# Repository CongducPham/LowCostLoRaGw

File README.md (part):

Low-cost LoRa IoT framework developed in the EU H2020 WAZIUP/WAZIHUB projects
=====================================================================

We are not maintaining this repo anymore
----------------------------------------

First of all, thank you for all the stars you gave us! We started the work on low-cost LoRa gateway back in 2015. It has been a great challenge for us and we learned a lot. We also hope that this early work has been useful for you in your projects. As we collaborated with WAZIUP e.V. on the development of a more efficient gateway software, some of our code served as foundation for a new development line called WaziGate by WAZIUP e.V. team who is doing a great work! In 2021, we completely shifted to this WaziGate distribution to build the edge-enabled LoRa gateway for the [PRIMA INTEL-IRRIS project](https://intel-irris.eu). You can read more detail on the dedicated [INTEL-IRRIS GitHub repo](https://github.com/CongducPham/PRIMA-Intel-IrriS). Then, in 2025, as our works in INTEL-IRRIS are continuing in the [PEPR AgriFutur project](https://iotsensingsystem.live-website.com/pepr-agroeconum-agrifutur), at time of writing, the latest edge-enabled gateway we are building on top of the general WaziGate framework provided by WAZIUP e.V is available from the dedicated [PEPR AgriFutur GitHub](https://github.com/CongducPham/PEPR_AgriFutur). Check our latest development on this GitHub repo. 

News from EU commission
-----------------------

- April 12th, 2022. European Internet of Things technology supports innovation in Africa: [two EU-Africa innovation projects have succeeded in rolling out advanced digital technologies to support entrepreneurship in sub-Saharan Africa](https://digital-strategy.ec.europa.eu/en/news/european-internet-things-technology-supports-innovation-africa).

- June 19th, 2020. The low-cost, low-power and long-distance cattle collar developed in the EU H2020 WAZIUP project has been identified by the European Commission's Innovation Radar! See more information at the end of this page.

Latest news
-----------

- **NEW-Dec22** Both the 32-bit OS and the 64-bit OS have now been upgraded and tested for RPI4 (including CM4). See [README](https://github.com/CongducPham/LowCostLoRaGw/blob/master/gw_full_latest/README-WiringPi-64bit-OS.md) for RPI4 and/or 64-bit OS.

- **NEW-Oct21** We have now a beta version of the whole low-cost Raspberry-based gateway with embedded advanced AI frameworks. The embedded AI framework will be used in PRIMA [INTEL-IRRIS project](http://intel-irris.eu/) to build low-cost and smart irrigation systems for smallholders. Follow INTEL-IRRIS [Twitter channel](https://twitter.com/Intel_IrriS) for updates. See [README](https://github.com/CongducPham/LowCostLoRaGw/blob/master/gw_full_latest/README-AI.md) on AI framework. Download the 64-bit RaspiOS SD image to be flashed on a 32GB class 10 SD card, see below for download links.

- **NEW-Jan21** To provide support for next 64-bit OS, the low-level SPI library on the Raspberry gateway has moved from Libelium's `arduPi` lib to Gordon's `wiringPi` lib because `arduPi` relies heavily on direct memory accesses that are difficult to port. The main reason for 64-bit OS is to prepare the whole low-cost Raspberry-based gateway to embed advanced AI frameworks that are mostly based on 64-bit OS. See [README](https://github.com/CongducPham/LowCostLoRaGw/blob/master/gw_full_latest/README-WiringPi-64bit-OS.md) for RPI4 and/or 64-bit OS. **`wiringPi` is now the default low-level SPI layer in the GitHub source distribution.**

- **NEW-Nov20** To support the new SX126X and SX128X LoRa chips, we updated and added Arduino ProMini PCBs to easily connect NiceRF SX1262 and NiceRF SX1280 modules. These modules have same size than the HopeRF RFM95W for SX1276.

- **NEW-Oct20** The low-level radio communication library has moved to the SX12XX LoRa library from Stuart Robinson in order to build devices and gateways with **SX126X, SX127X and SX128X LoRa chip**. The default gateway program is compiled for an SX127X based module using the SX12XX library. This is a major move to provide support for the most recent LoRa chips including those for 2.4GHz LoRa. See [README](https://github.com/CongducPham/LowCostLoRaGw/blob/master/gw_full_latest/README-SX12XX.md) on porting to SX12XX library.

Quick start
-----------
- **Beta version of RaspiOS (Debian Buster 64-bit) with AI framework is ready for testing!** It has everything you need (all features of 32-bit version) + the embedded AI framework. [zipped 8GB SD card image from GoogleDrive](https://drive.google.com/uc?export=download&id=1UzSULM2TjCKWjVWIvHqLy6Iu_FR_1Xmo). The image is about 3GB for download. You can take the 8GB image for flashing on 16GB or 32GB SD card and use `raspi-config` to expand the file system. 
- **The current SD card image (Debian Buster 32-bit) has everything you need!** [zipped 8GB SD card image from GoogleDrive](https://drive.google.com/uc?export=download&id=1ZiIpA_PfARHPmQetJ25iZnfyjeD8Rm3j). To be flashed on a 8GB class 10 SD card. See [installation section](https://github.com/CongducPham/LowCostLoRaGw#installing-the-latest-gateway-version). 
- Use the single-channel gateway for LoRaWAN-like communication (including downlink) with LoRa 2.4GHz. Upload to TTN or ChirpStack network servers. See [README](https://github.com/CongducPham/LowCostLoRaGw/blob/master/gw_full_latest/README-SX12XX.md)
- Use the single-channel gateway for limited LoRaWAN (including downlink and OTAA feature) on the 433MHz band for devices with our [modified LMIC](https://github.com/CongducPham/LMIC_low_power#using-433mhz-band)
- The single-channel gateway now also provides LoRaWAN downlink and OTAA features for devices with our [modified LMIC](https://github.com/CongducPham/LMIC_low_power#using-single-channel-gateway). See updated [README](https://github.com/CongducPham/LowCostLoRaGw/blob/master/gw_full_latest/README-downlink.md)
- Includes support of the open-source ChirpStack LoRaWAN Network Server, see [README](https://github.com/CongducPham/LowCostLoRaGw/blob/master/gw_full_latest/scripts/chirpstack/README.md)
- Support of multi-channel RPI SX1301 LoRaWAN gateway: benefit from the open, versatile, multi-cloud Low-cost LoRa IoT framework with the flexibility and scalability of a multi-channel LoRaWAN gateway, see [README](https://github.com/CongducPham/LowCostLoRaGw/blob/master/gw_full_latest/scripts/rak2245-rak831/README.md)
- We have a new online [Arduino-Sensor-LoRa tutorial](http://cpham.perso.univ-pau.fr/LORA/WAZIUP/tuto/index.html) and here is the direct link to the [LoRa part](http://cpham.perso.univ-pau.fr/LORA/WAZIUP/tuto/sensors/lora_sensor/Arduino_lora_demo.html)
- Read the [Low-cost-LoRa-device leaflet](https://github.com/CongducPham/tutorials/blob/master/Low-cost-LoRa-device-leaflet.pdf)
- Read the [Low-cost-LoRa-GW leaflet](https://github.com/CongducPham/tutorials/blob/master/Low-cost-LoRa-GW-leaflet.pdf)
- Look at the [Low-cost-LoRa-GW web admin interface tutorial](https://github.com/CongducPham/tutorials/blob/master/Low-cost-LoRa-GW-web-admin.pdf). For most end-users, the web admin interface is sufficient to configure and manage the gateway. **For instance, to configure a new gateway, it is recommended to use the web admin interface to update the gateway software and to run the basic configuration procedure as described [here](https://github.com/CongducPham/LowCostLoRaGw#option-i)**
- **The rest of this README file contains additional information to better understand the proposed low-cost IoT framework**.

PCBs
----

In order to facilitate connection between an Arduino board or a RaspberryPI and the well-known RFM95W (SX1276) LoRa radio module, we developed simple PCBs for Arduino ProMini, Arduino Nano and RaspberryPI and make them **freely** available. 

The first PCB is a simple RFM95W breakout with header pins for both the Raspberry (mainly to make a gateway) and Arduino boards. The RFM95W breakout initially designed for the HopeRF RFM95W (referred to as old RFM95W breakout) can actually also host the recent NiceRF SX1262 as both radio modules have similar pinout. However, we updated the old RFM95W breakout's wiring to also expose DIO2 and DIO1 on the Raspberry header to better support the NiceRF SX1262 module (DIO2 location on the RFM95W is the BUSY pin on the NiceRF SX1262 and DIO1 pin is used for RX/TX done interrupt on the NiceRF SX1262 instead of the DIO0 pin on the RFM95W). BUSY pin is needed for the SX126X so if you are using the old RFM95W breakout you need to solder a wire. Our modified communication library does not need DIO1 pin. When updating the RFM95W breakout we also added a 4-pin header to easily connect a small OLED screen to a Raspberry using the I2C bus (SCL and SDA pin).

We also made a variant to support the NiceRF SX1280 module which provides LoRa modulation on the 2.4GHz band (I really don't know why the SX1280 did not use the same pinout than the SX1262 which is similar to the RFM95W!). All these breakout PCBs are illustrated in the following figure.

These PCBs can therefore be connected to the GPIO header row of the Raspberry as shown below. Pins on the Raspberry for RST, CS (or NSS), DIO2/BUSY and DIO1 are shown.

These breakouts can also be used for Arduino boards as it will be explained in Section [connect a radio module to your end-device](https://github.com/CongducPham/LowCostLoRaGw#connect-a-radio-module-to-your-end-device) and illustrated below. On the breakout's Arduino header, you can connect RFM95's DIO0 to a digital pin of your Arduino if you want to use another communication library that needs this pin. For NiceRF SX1262 and NiceRF SX1280 you can get BUSY and DIO1 pins from the Raspberry header with the updated design. BUSY pin is needed but our modified communication library does not need DIO1 pin. 

However, for Arduino, it is more convenient to use our dedicated Arduino Nano/ProMini PCBs illustrated below. The PCB for Arduino Nano is mainly intended for teaching/training purpose as the Nano is not energy-efficient enough for real deployment. However its main advantage is to avoid the need of an external FTDI breakout cable to program it. It has not been updated for a while and we are not really maintaining it anymore. You can find in the PCB folder the EAGLE schematic file (NanoLoRaBreakout_2019-05-14.sch) if you want to modify the design yourself.

The PCB for the Arduino ProMini (3.3v, 8MHz version) can be used for prototyping and even integration purpose. Beware that A4 and A5 (which are usually SDA and SCL pin of the I2C bus) are not connected on the PCB. If you need to use them, use these 2 pins from the Arduino board itself. The PCB for the Arduino ProMini has been updated several times. The last version is v3 for both RFM95W and NiceRF SX1262 and v2 for NiceRF SX1280.

All the PCBs have footprint for an SMA connector or uFl. Both Nano and ProMini PCBs have replicated rows for all the pins. They also have extra VCC and GND rails. They also have 4 solder pads that can be soldered together if you want to connect various DIO pins. Some of these pads are by default connected. If you want to use the connected Arduino pins for other purposes, just cut the wire between the pads with a cutter and test for discontinuity.

- for RFM95W. Connected by default: DIO0 to D2, DIO1 to D3, RST to D4. Not connected by default: DIO2 to D5
- for NiceRF SX1262. Connected by default: DIO1 to D3, RST to D4. Not connected by default: BUSY to D5
- for NiceRF SX1280. Connected by default: DIO1 to D2, BUSY to D3 and RST to D4. Not connected by default: DIO2 to D5 

Our modified communication library makes wiring a bit easier because only CS, MISO, MOSI, SCK, BUSY (SX126X and SX128X only) and RST are needed. However on the PCBs, DIOs pins are available to use other libraries (for LMIC stack for instance). We also indicate clearly which pin of the LoRa module you need to solder on the PCB (for instance `MOSI>`). As you can see on the picture, you can directly solder the Arduino board on the PCB, or, as we did, use intermediate headers so that the Arduino board can be easily plugged and removed.

You can download all the Gerber zipped archive and view them on an [online Gerber viewer](https://www.pcbgogo.com/GerberViewer.html).

- RFM95W/NiceRF SX1262 breakout zipped Gerber archive, 2 layer board of 29x37mm [.zip](https://github.com/CongducPham/LowCostLoRaGw/raw/master/PCBs/RFM95Breakout_2020-11-14.zip)
- NiceRF SX1280 breakout zipped Gerber archive, 2 layer board of 29x37mm [.zip](https://github.com/CongducPham/LowCostLoRaGw/raw/master/PCBs/SX1280Breakout_2020-11-14.zip)
- Arduino Nano v2 PCB for RFM95W zipped Gerber archive, 2 layer board of 30x81mm [.zip](https://github.com/CongducPham/LowCostLoRaGw/raw/master/PCBs/NanoLoRaBreakout_2019-05-14.zip)
- Arduino ProMini v3 PCB for RFM95W/NiceRF SX1262 zipped Gerber archive, 2 layer board of 30x77mm [.zip](https://github.com/CongducPham/LowCostLoRaGw/raw/master/PCBs/ProMiniLoRaBreakout_2020-11-14.zip)
- Arduino ProMini v2 PCB for NiceRF SX1280 zipped Gerber archive, 2 layer board of 30x77mm [.zip](https://github.com/CongducPham/LowCostLoRaGw/raw/master/PCBs/ProMiniLoRaBreakoutSX1280_2020-11-14.zip)

You can easily make them produced on many online PCB manufacturers. Usually, you just need to provide the zip archive and both size and number of layers are detected. You can dramatically decrease the price by using "panelize" option. As you can see on the pictures, we use 3x2 for the RFM95 breakout and 3x1 for both the Nano and ProMini PCBs. For instance, we ordered them from [JLCPCB](https://jlcpcb.com/) and the cost of 10 panels (i.e. 60 RFM95W breakout or 30 Nano/ProMini breakout) is about $4!

Tutorial materials
------------------

1 online tutorial

- [Arduino-Sensor-LoRa tutorial](https://cpham.perso.univ-pau.fr/LORA/WAZIUP/tuto/index.html)

3 tutorial videos on YouTube: video of all the steps to build the whole framework from scratch

- [Build your low-cost, long-range IoT device with WAZIUP](https://www.youtube.com/watch?v=YsKbJeeav_M)
- [Extreme low-cost & low-power LoRa IoT for real-world deployment](https://www.youtube.com/watch?v=2_VQpcCwdd8)
- [Build your low-cost LoRa gateway with WAZIUP](https://www.youtube.com/watch?v=mj8ItKA14PY)

1 live demo video on YouTube: setting up a gateway in less than 5 mins to upload data to various clouds

- [Setting up a LoRa gateway in less than 5mins (live demo)](https://www.youtube.com/watch?v=CJbUFXLpSok)

Go to [https://github.com/CongducPham/tutorials](https://github.com/CongducPham/tutorials) for all tutorials and particularly look for:

- [Low-cost-LoRa-GW-outdoor](https://github.com/CongducPham/tutorials/blob/master/Low-cost-LoRa-GW-outdoor.pdf)
- [Low-cost-LoRa-GW leaflet](https://github.com/CongducPham/tutorials/blob/master/Low-cost-LoRa-GW-leaflet.pdf)
- [Low-cost-LoRa-device leaflet](https://github.com/CongducPham/tutorials/blob/master/Low-cost-LoRa-device-leaflet.pdf)
- [Low-cost-LoRa-IoT-step-by-step tutorial](https://github.com/CongducPham/tutorials/blob/master/Low-cost-LoRa-IoT-step-by-step.pdf) 
- [Low-cost-LoRa-GW-step-by-step tutorial](https://github.com/CongducPham/tutorials/blob/master/Low-cost-LoRa-GW-step-by-step.pdf)
- [Low-cost-LoRa-GW web admin interface tutorial](https://github.com/CongducPham/tutorials/blob/master/Low-cost-LoRa-GW-web-admin.pdf)
- [Low-cost-LoRa-IoT-antennaCable tutorial](https://github.com/CongducPham/tutorials/blob/master/Low-cost-LoRa-IoT-antennaCable.pdf)

Look also at our [FAQ](https://github.com/CongducPham/tutorials/blob/master/FAQ.pdf)!

Also consult the following web page: http://cpham.perso.univ-pau.fr/LORA/RPIgateway.html.

Main features of gateway
------------------------

- **NEW** There is a 64-bit version to better embed AI frameworks.
- **NEW** The low-level radio communication library has moved to the SX12XX LoRa library from Stuart Robinson in order to build devices and gateways with **SX126X, SX127X and SX128X LoRa chip**.
- **NEW** The single-channel gateway now also provides LoRaWAN downlink and OTAA features
	- see [README](https://github.com/CongducPham/LowCostLoRaGw/blob/master/gw_full_latest/README-downlink.md)
- **NEW** Integration and easy configuration of the open-source ChirpStack Network Server as local Network Server
	- see [README](https://github.com/CongducPham/LowCostLoRaGw/blob/master/gw_full_latest/scripts/chirpstack/README.md)
- **NEW** Support of multi-channel RPI SX1301 LoRaWAN gateway
	- benefit from the open, versatile, multi-cloud Low-cost LoRa IoT framework with the flexibility and scalability of a multi-channel LoRaWAN gateway
	- see [README](https://github.com/CongducPham/LowCostLoRaGw/blob/master/gw_full_latest/scripts/rak2245-rak831/README.md)
- support of LoRaWAN and connection to LoRaWAN cloud (e.g. TTN platform)
	- see [README](https://github.com/CongducPham/LowCostLoRaGw/blob/master/gw_full_latest/README-TTN.md) for TTN support and configuration
	- see this [section](https://github.com/CongducPham/LowCostLoRaGw/tree/master/Arduino#lorawan-example-and-support) for the device side
	- see [README](https://github.com/CongducPham/LowCostLoRaGw/blob/master/gw_full_latest/README-aes_lorawan.md) for updated info on LoRaWAN and data AES encryption
- simple, flexible and generic cloud management approach
	- [README](https://github.com/CongducPham/LowCostLoRaGw/blob/master/gw_full_latest/README-NewCloud.md)
	- look at the provided cloud script examples to see how IoT clouds such as TTN, ThingSpeak, GroveStreams, MQTT,... are supported
	- a cloud script can be used to generalize the upload of data using SMS, ftp, file, MQTT, Node-Red flow,...		
- remote access to your gateway from anywhere: `remot3.it`, `ngrok`
	- [README](https://github.com/CongducPham/LowCostLoRaGw/blob/master/gw_full_latest/README-remote-access-remot3it.md)
	- [README](https://github.com/CongducPham/LowCostLoRaGw/blob/master/gw_full_latest/README-remote-access-ngrok.md)
- a simple, user-friendly web admin interface to configure and update your gateway
	- open a browser and go to http://`gw_ip_address`/admin
	- [README](https://github.com/CongducPham/LowCostLoRaGw/blob/master/gw_full_latest/gw_web_admin/README.md)
	- [Tutorial](https://github.com/CongducPham/tutorials/blob/master/Low-cost-LoRa-GW-web-admin.pdf)
	- `raspap-webgui` from https://github.com/billz/raspap-webgui has been integrated and can be accessed at http://`gw_ip_address`/raspap-webgui. When the gateway is configured as a WiFi client, `raspap-webgui` is especially useful to dynamically discover and configure additional WiFi networks. Read this [section](https://github.com/CongducPham/LowCostLoRaGw/tree/master/gw_full_latest#make-your-gateway-a-wifi-client) prior to use `raspap-webgui`.	
- a NoSQL MongoDB database stores received data for local/edge processing. See [here](https://github.com/CongducPham/LowCostLoRaGw/blob/master/gw_full_latest/README-NewCloud.md#support-of-mongodb-as-a-cloud-declaration) for more information on the local MongoDB structure.
- the gateway acts as the WiFi access-point. The SSID is `WAZIUP_PI_GW_XXXXXXXXXX` where `XXXXXXXXXX` is the last 6 hex bytes of gateway ID: `WAZIUP_PI_GW_B827EB27F90F` for instance. It has IP address 192.168.200.1 and will lease IP addresses in the range of 192.168.200.100 and 192.168.200.120.
- there is an Apache web server with basic PHP forms to visualize graphically the received data of the MongoDB with any web browser. Just connect to http://192.168.200.1 with a web browser (could be from a smartphone) to get the graphic visualization of the data stored in the gateway's MongoDB database.
- a captive WiFi portal can be installed to automatically land on http://192.168.200.1 (default setting)
	- [README](https://github.com/CongducPham/LowCostLoRaGw/blob/master/gw_full_latest/splash/README.md)
- by default, incoming data are uploaded to our [LoRa ThingSpeak test channel](https://thingspeak.com/channels/66794)
- works out-of-the-box with the [Arduino_LoRa_Simple_temp sketch](https://github.com/CongducPham/LowCostLoRaGw/tree/master/Arduino/Arduino_LoRa_Simple_temp)

Manually connect a radio module to the Raspberry
=======================================

If you want to manually connect a LoRa radio module to the Raspberry's GPIO header, just connect the corresponding SPI pin (MOSI, MISO, CLK, CS) and the reset (RST) pin.

```
      RPI            Radio module
   GND pin 25----------GND   (ground in)
   3V3 pin 17----------3.3V  (3.3V in)
 GPIO4 pin  7----------RST   (Reset) 
CS/CE0 pin 24----------NSS   (CS chip select in)
   SCK pin 23----------SCK   (SPI clock in)
  MOSI pin 19----------MOSI  (SPI Data in)
  MISO pin 21----------MISO  (SPI Data out)
```

You can have a look at the "Low-cost-LoRa-GW-step-by-step" tutorial in our tutorial repository https://github.com/CongducPham/tutorials.

**Or you can of course use our RFM95W/NiceRF SX1262 and NiceRF SX1280 breakouts that can be directly connected to the Raspberry GPIO header**. Look also at our [Low-cost-LoRa-GW-outdoor](https://github.com/CongducPham/tutorials/blob/master/Low-cost-LoRa-GW-outdoor.pdf) tutorial to build an outdoor gateway.

Installing the latest gateway version 
=====================================

The full, latest distribution of the low-cost gateway is available in the `gw_full_latest` folder of the github repository: https://github.com/CongducPham/LowCostLoRaGw. It contains all the gateway control and post-processing software. 

However, the **simplest and recommended way** to install a new gateway is to use [zipped 8GB SD card image from GoogleDrive](https://drive.google.com/uc?export=download&id=1Euuo4tPJrz6EHGFQ7IsCrWJbmJmHgLJR) based on the Buster Raspbian OS and perform a new install of the gateway from this image. In this way you don't need to install the various additional packages that are required (as explained in an additional [README](https://github.com/CongducPham/LowCostLoRaGw/blob/master/gw_full_latest/README-manual-install.md) describing all manual installation steps if you want to install from scratch). Once you have burnt the SD image on a 8GB (minimum) SD card, insert it in your Raspberry and power it.

The distribution supports all RPI models including the last RPI4. There is out-of-the-box WiFi support for RPI4B/3B/3B+ and RPI0W. For RPI1 and RPI2 see [here](https://github.com/CongducPham/LowCostLoRaGw/blob/master/gw_full_latest/README.md#wifi-instructions-on-rpi1b-and-rpi2) for modifications to support some WiFi dongles.

Get our SD card image
---------------------

Download our 32-bit ([zipped 8GB SD card image from GoogleDrive](https://drive.google.com/uc?export=download&id=1ZiIpA_PfARHPmQetJ25iZnfyjeD8Rm3j)) or 64-bit ([zipped 8GB SD card image from GoogleDrive](https://drive.google.com/uc?export=download&id=1UzSULM2TjCKWjVWIvHqLy6Iu_FR_1Xmo)). It has everything you need including:

- support for all RPI models including the last RPI4 as well. We recommend the RPI 3B model for a simple IoT gateway and a 3B+/4 for using embedded AI processing. However, the latter consume more power and are heating a lot more.
- pre-installed open-source ChirpStack LoRaWAN Network Server
- pre-installed Semtech's `lora_pkt_fwd` for multi-channel gteway
- pre-installed `remot3.it` and `anydesk` tools for remote access (only 32-bit)
- the simple gateway web admin interface for easy configuration and management
- `mosquitto-clients` package installed to have `mosquitto_pub` and `mosquitto_sub` commands
- `Node-RED`, `Node.js` and `npm` with `node-red-contrib-thingspeak42` installed
- a ready-to-use Node-RED flow to show how received data can be uploaded to MQTT brokers and ThingSpeak
- MongoDB 

Simply unzip the file and burn the ISO file to an SD card. Take a class 10 (it is more than recommended!). If you have bigger SD card, then after boot, use `raspi-config` (see [tutorial here](https://www.raspberrypi.org/documentation/configuration/raspi-config.md)) to resize the partition in order to use the extra space available (you will need to reboot but `raspi-config` will ask you for that). You can use `df -h` to verify that you have more space after reboot.  

You can look at various tutorials on how to burn an image to an SD card. There is one [here from raspberrypi.org](https://www.raspberrypi.org/documentation/installation/installing-images/) and [here from elinux.org](http://elinux.org/RPi_Easy_SD_Card_Setup). We use a Mac to do so and [this is our preferred solution](https://www.raspberrypi.org/documentation/installation/installing-images/mac.md). The [Linux version](https://www.raspberrypi.org/documentation/installation/installing-images/linux.md) is not very different. The `Balena Etcher` tool is also very nice and you don't even need to unzip the SD card image. We also use that solution extensively.

When booting from the provided SD card image
============================================ 

**Important notice**: the LoRa gateway program starts automatically when the Raspberry is powered on. 

**You can try your gateway right away now by building your end-device and jump directly to this [section](https://github.com/CongducPham/LowCostLoRaGw#connect-a-radio-module-to-your-end-device)**.

If you want to connect (`ssh`) to the gateway and perform update procedure, read the rest of the section.
	
Connect to your new gateway
---------------------------

The SD card image defines a `pi` user:

	- login: pi
	- password: loragateway
		
With the default gateway configuration, the gateway acts as a WiFi access point. If you see the WiFi network `WAZIUP_PI_GW_XXXXXXXXXX` then connect to this WiFi network. The WiFi password is `loragateway`. **It is strongly advise to change this WiFi password**. The address of the Raspberry is then 192.168.200.1. Note that it is very convenient to use a smartphone or a tablet to connect to your gateway with `ssh`. On iOS we tested `Termius`  and on Android we tested `JuiceSSH`.

If you see no WiFi access point (e.g. RP1/RPI2/RPI0 without WiFi dongle), then plug your Raspberry into a DHCP-enabled box/router/network to get an IP address or shared your laptop internet connection to make your laptop acting as a DHCP server. On a Mac, there is a very simple solution [here](https://mycyberuniverse.com/mac-os/connect-to-raspberry-pi-from-a-mac-using-ethernet.html). For Windows, you can follow [this tutorial](http://www.instructables.com/id/Direct-Network-Connection-between-Windows-PC-and-R/) or [this one](https://electrosome.com/raspberry-pi-ethernet-direct-windows-pc/). You can then use [Angry IP Scanner](http://angryip.org/) available on Windows/Mac/Linux/Android to determine the assigned IP address for the Raspberry.

We will use in this example 192.168.2.8 for the gateway address (DHCP option in order to have Internet access from the Raspberry)

	> ssh pi@192.168.2.8
	pi@192.168.200.1's password: 
	
	The programs included with the Debian GNU/Linux system are free software;
	the exact distribution terms for each program are described in the
	individual files in /usr/share/doc/*/copyright.
	
	Debian GNU/Linux comes with ABSOLUTELY NO WARRANTY, to the extent
	permitted by applicable law.
	Last login: Thu Aug  4 18:04:41 2016
	
**For the Raspberry Zero**, our SD card image set the RPI in access point mode. However, when in access-point mode, Ethernet over USB with `dtoverlay=dwc2` in `/boot/config.txt` and `modules-load=dwc2,g_ether` in `/boot/cmdline.txt` is not working. As the usage of the Raspberry Zero is mainly with Internet connection through a cellular network (using for instance the LORANGA board from La Fabrica Alegre) the easiest way to have Internet through Ethernet sharing with our SD card image is to use a USB-Ethernet adapter that will add an eth0 interface on the RPI0. These USB-Ethernet adapter are quite cheap and are really useful on the RPI0 as you can then connect it to a DHCP-enabled router/box just like the other RPI boards. Alternatively, you can set your gateway as a WiFi client to connect to an existing WiFi network, see [here](https://github.com/CongducPham/LowCostLoRaGw/tree/master/gw_full_latest#make-your-gateway-a-wifi-client).

Upgrade to the latest gateway version	
-------------------------------------

Once you have your SD card flashed with our image, to get directly to the full, latest gateway version, you can either use (i) the web admin interface, or (ii) the provided update script to be run from the gateway, or (iii) download (git clone) the whole repository and copy the entire content of the gw_full_latest folder on your Raspberry, in a folder named `lora_gateway` or, (iv) get only (`svn checkout`) the `gw_full_latest` folder in a folder named `lora_gateway`. Option (i) is recommended and simple while (ii) is basically an automatization of option (iii) in command line mode. Both options (i) and (ii) however need Internet connectivity on the gateway while option (iii) and (iv) can be done on a computer prior to copy the files on the Raspberry.

Option (i)
----------

**It is the recommended option but the Raspberry must have Internet connection**.

Choose the `Gateway Update` menu on the left. Then, if you install a brand new gateway with our SD card image, use `New installation`. For future updates, use `Full update`.

After `New installation` or `Full update`, run `Basic config`.

When using the web interface, you don't need to perform the manual `Configuring your gateway after update` step below.

It is also recommended to run `Update web admin interface` to update the web interface to the last version, after `New installation` or `Full update`.

Then reboot.

**The full LoRa gateway with post-processing stage starts automatically when the Raspberry is powered on**. By default, incoming data are uploaded to our [LoRa ThingSpeak test channel](https://thingspeak.com/channels/66794). It will work out-of-the-box with the [Arduino_LoRa_Simple_temp sketch](https://github.com/CongducPham/LowCostLoRaGw/tree/master/Arduino/Arduino_LoRa_Simple_temp).

Option (ii)
-----------

If your gateway has Internet connectivity (DHCP with Internet sharing on your laptop for instance), you can use our `update_gw.sh` script. Even if the SD card image has a recent version of the gateway software with the `update_gw.sh` script in the `lora_gateway/scripts` folder it is safer to get the latest version of this script. Simply do:

	> cd /home/pi
	> wget https://raw.githubusercontent.com/CongducPham/LowCostLoRaGw/master/gw_full_latest/scripts/update_gw.sh
	> chmod +x update_gw.sh
	> sudo ./update_gw.sh
	
Note that if you have customized configuration files (i.e. `key_*`, `gateway_conf.json`, `clouds.json` and `radio.makefile`) in the existing `/home/pi/lora_gateway` folder, then `update_gw.sh` will preserve all these configuration files. As the repository does not have a `gateway_id.txt` file, it will also preserve your gateway id.

Otherwise, if it is really the first time you install the gateway, then you can delete the `lora_gateway` folder before running the script:

	> rm -rf lora_gateway
	> sudo ./update_gw.sh

Option (iii)
------------

This upgrade solution can be done on the Raspberry if it has Internet connectivity or on your laptop which is assumed to have Internet connectivity. If you don't have git installed on your laptop, you have to install it first. Then get all the repository:

	> cd /home/pi
	> git clone https://github.com/CongducPham/LowCostLoRaGw.git
	
You will get the entire repository:

	pi@raspberrypi:~ $ ls -l LowCostLoRaGw/
	total 32
	drwxr-xr-x 7 pi pi  4096 Apr  1 15:38 Arduino
	-rw-r--r-- 1 pi pi 15522 Apr  1 15:38 README.md	
	drwxr-xr-x 2 pi pi  4096 Apr  1 15:38 gw_full_latest	
	drwxr-xr-x 2 pi pi  4096 Apr  1 15:38 tutorials
	
Create a folder named `lora_gateway` (or if you already have one, then delete all its content) then copy all the files of the `LowCostLoRaGw/gw_full_latest` folder in it.

    > mkdir lora_gateway
    > cd lora_gateway
    > cp -R ../LowCostLoRaGw/gw_full_latest/* .
    
Or if you want to "move" the `LowCostLoRaGw/gw_full_latest` folder, simply do (without creating the `lora_gateway` folder before):

	> mv LowCostLoRaGw/gw_full_latest ./lora_gateway  
	
If you download the repository from your laptop, then rename `gw_full_latest` into `lora_gateway` and copy the entire `lora_gateway` folder into the Raspberry using `scp` for instance. In the example below, the laptop has wired Internet connectivity and use the gateway's advertised WiFi to connect to the gateway. Therefore the IP address of the gateway is 192.168.200.1.

	> scp -r lora_gateway pi@192.168.200.1:/home/pi
	
If you don't want to use/install `git`, use your laptop to get the .zip file of the [entire github](https://github.com/CongducPham/LowCostLoRaGw) with the "Clone or download" option, unzip the package, rename the `gw_full_latest` folder as `lora_gateway` and perform the `scp` command.		  

Option (iv)
-----------

This upgrade solution can be done on the Raspberry if it has Internet connectivity or on your laptop which is assumed to have Internet connectivity. If you don't have `svn` installed on your laptop, you have to install it first. Then get only the gateway part:

	> cd /home/pi
	> svn checkout https://github.com/CongducPham/LowCostLoRaGw/trunk/gw_full_latest lora_gateway
	
That will create the `lora_gateway` folder and get all the file of (GitHub) `LowCostLoRaGw/gw_full_latest` in it. 
	
To install `svn` on the Raspberry:

	> sudo apt-get install subversion	
	
Here, again, you can do all these steps on your laptop and then use `scp` to copy to the Raspberry.	

Configuring your gateway after update
-------------------------------------

After gateway update with option (ii), (iii) or (iv), you need to configure your new gateway with `basic_config_gw.sh`, that mainly assigns the gateway id so that it is uniquely identified (the gateway's WiFi access point SSID is based on that gateway id for instance). The gateway id will be the last 6 bytes of the Rapberry eth0 MAC address (or wlan0 on an RPI0W without Ethernet adapter) and the configuration script will extract this information for you. There is an additional script called `test_gwid.sh` in the script folder to test whether the gateway id can be easily determined. In the `scripts` folder, simply run `test_gwid.sh`:

	> cd /home/pi/lora_gateway/scripts
	> ./test_gwid.sh
	Detecting gw id as 0000B827EBBEDA21
	
If you don't see something similar to 0000B827EBBEDA21 (8 bytes in hex format) then you have to explicitly provide the **last 6 bytes**	of the gw id to `basic_config_gw.sh`. Otherwise, in the `scripts` folder, simply run `basic_config_gw.sh` to automatically configure your gateway. 

	> cd /home/pi/lora_gateway/scripts
	> ./basic_config_gw.sh
	
or

	> ./basic_config_gw.sh B827EBBEDA21

If you need more advanced configuration, then run `config_gw.sh` as described [here](https://github.com/CongducPham/LowCostLoRaGw/tree/master/gw_full_latest#configure-your-gateway-with-basic_config_gwsh-or-config_gwsh). However, `basic_config_gw.sh` should be sufficient for most of the cases. The script also compile the low-level gateway program corresponding to you Raspberry model. After configuration, reboot your Raspberry. 

By default `gateway_conf.json` configures the gateway with a simple behavior: LoRa mode 1 (BW125SF12), no DHT sensor in gateway (so no MongoDB for DHT sensor), no downlink, no AES, no raw mode. `clouds.json` enables only the ThingSpeak demo channel (even the local MongoDB storage is disabled). You can customize your gateway later when you have more cloud accounts and when you know better what features you want to enable.

The LoRa gateway starts automatically when RPI is powered on. Then use `cmd.sh` to execute the main operations on the gateway as described [here](https://github.com/CongducPham/LowCostLoRaGw/blob/master/gw_full_latest/README.md#use-cmdsh-to-interact-with-the-gateway).	

Connect a radio module to your end-device
=========================================

To have an end-device, you have to connect a LoRa radio module to an Arduino board. Just connect the corresponding SPI pin (MOSI, MISO, CLK, CS/SS) and the RST pin. On the Uno, Pro Mini, Mini, Nano, Teensy the mapping is as follows:

```
       Arduino      Radio module
         GND----------GND   (ground in)
         3V3----------3.3V  (3.3V in)
  SS pin D10----------NSS   (CS chip select in)
 SCK pin D13----------SCK   (SPI clock in)
MOSI pin D11----------MOSI  (SPI Data in)
MISO pin D12----------MISO  (SPI Data out)
          D4----------RST   (Reset)
```

**For the Nano and the ProMini, you can of course use our Nano/ProMini PCBs that makes connection to an RFM95W/NiceRF SX1262 and NiceRF SX1280 radio straightforward**.

On the MEGA, the SPI pin are as follows: 50 (MISO), 51 (MOSI), 52 (SCK). Starting from November 3rd, 2017, the CS pin is always pin number 10 on Arduino and Teensy boards. You can have a look at the [Low-cost-LoRa-IoT-step-by-step](https://github.com/CongducPham/tutorials/blob/master/Low-cost-LoRa-IoT-outdoor-step-by-step.pdf) tutorial in the tutorial repository https://github.com/CongducPham/tutorials.

There is an important issue regarding the radio modules. The Semtech SX1272/76 has actually 2 lines of RF power amplification (PA): a high efficiency PA up to 14dBm (RFO) and a high power PA up to 20dBm (PA_BOOST).

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
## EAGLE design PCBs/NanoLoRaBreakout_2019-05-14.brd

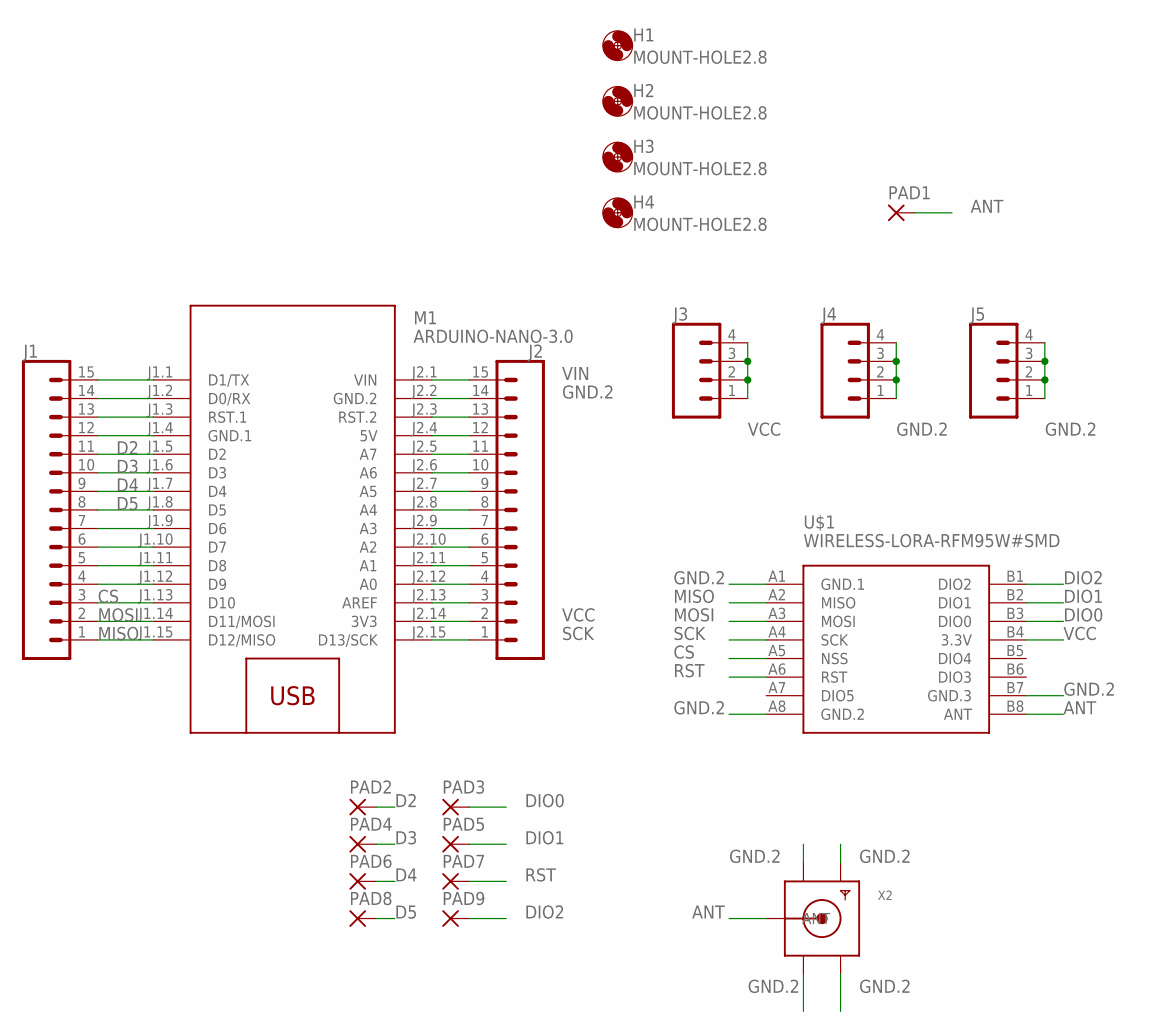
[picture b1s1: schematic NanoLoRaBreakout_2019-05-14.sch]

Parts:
H1, H2, H3, H4: MOUNT-HOLE2.8; 2,8
J1, J2: CONN_15; 1X15
J3, J4, J5: CONN_04; 1X04
M1: ARDUINO-NANO-3.0
PAD1: 1,6/0,8
PAD2, PAD3, PAD4, PAD5, PAD6, PAD7, PAD8, PAD9: SMD2; SMD1,27-2,54
U$1: WIRELESS-LORA-RFM95W#SMD
X2: SMACONNECTOR_EDGE_UFL; SMA_EDGELAUNCH_UFL

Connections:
ANT: PAD1.1, U$1.B8 (ANT), X2.P (ANT)
CS: J1.3, M1.J1.13 (D10), U$1.A5 (NSS)
D2: J1.11, M1.J1.5 (D2), PAD2.1
D3: J1.10, M1.J1.6 (D3), PAD4.1
D4: J1.9, M1.J1.7 (D4), PAD6.1
D5: J1.8, M1.J1.8 (D5), PAD8.1
DIO0: PAD3.1, U$1.B3 (DIO0)
DIO1: PAD5.1, U$1.B2 (DIO1)
DIO2: PAD9.1, U$1.B1 (DIO2)
GND.2: J2.14, J4.1, J4.2, J4.3, J4.4, J5.1, J5.2, J5.3, J5.4, M1.J2.2 (GND.2), U$1.A1 (GND.1), U$1.A8 (GND.2), U$1.B7 (GND.3), X2.GND@1 (GND1), X2.GND@2 (GND2), X2.GND@3 (GND3), X2.GND@4 (GND4)
MISO: J1.1, M1.J1.15 (D12/MISO), U$1.A2 (MISO)
MOSI: J1.2, M1.J1.14 (D11/MOSI), U$1.A3 (MOSI)
unnamed: J1.4, M1.J1.12 (D9)
unnamed: J1.5, M1.J1.11 (D8)
unnamed: J1.6, M1.J1.10 (D7)
unnamed: J1.7, M1.J1.9 (D6)
unnamed: J1.12, M1.J1.4 (GND.1)
unnamed: J1.13, M1.J1.3 (RST.1)
unnamed: J1.14, M1.J1.2 (D0/RX)
unnamed: J1.15, M1.J1.1 (D1/TX)
unnamed: J2.3, M1.J2.13 (AREF)
unnamed: J2.4, M1.J2.12 (A0)
unnamed: J2.5, M1.J2.11 (A1)
unnamed: J2.6, M1.J2.10 (A2)
unnamed: J2.7, M1.J2.9 (A3)
unnamed: J2.8, M1.J2.8 (A4)
unnamed: J2.9, M1.J2.7 (A5)
unnamed: J2.10, M1.J2.6 (A6)
unnamed: J2.11, M1.J2.5 (A7)
unnamed: J2.12, M1.J2.4 (5V)
unnamed: J2.13, M1.J2.3 (RST.2)
RST: PAD7.1, U$1.A6 (RST)
SCK: J2.1, M1.J2.15 (D13/SCK), U$1.A4 (SCK)
VCC: J2.2, J3.1, J3.2, J3.3, J3.4, M1.J2.14 (3V3), U$1.B4 (3.3V)
VIN: J2.15, M1.J2.1 (VIN)

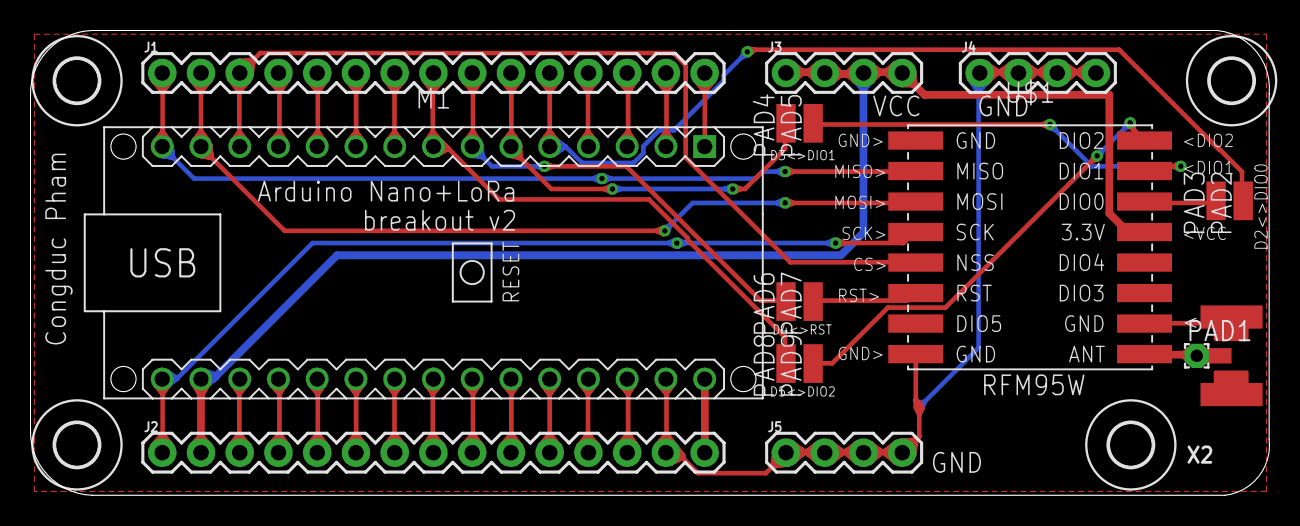
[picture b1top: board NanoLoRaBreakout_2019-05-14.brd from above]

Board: 2 copper layers, 81.2 x 30.5 mm, 21 parts (0 on the bottom side), 35 nets.

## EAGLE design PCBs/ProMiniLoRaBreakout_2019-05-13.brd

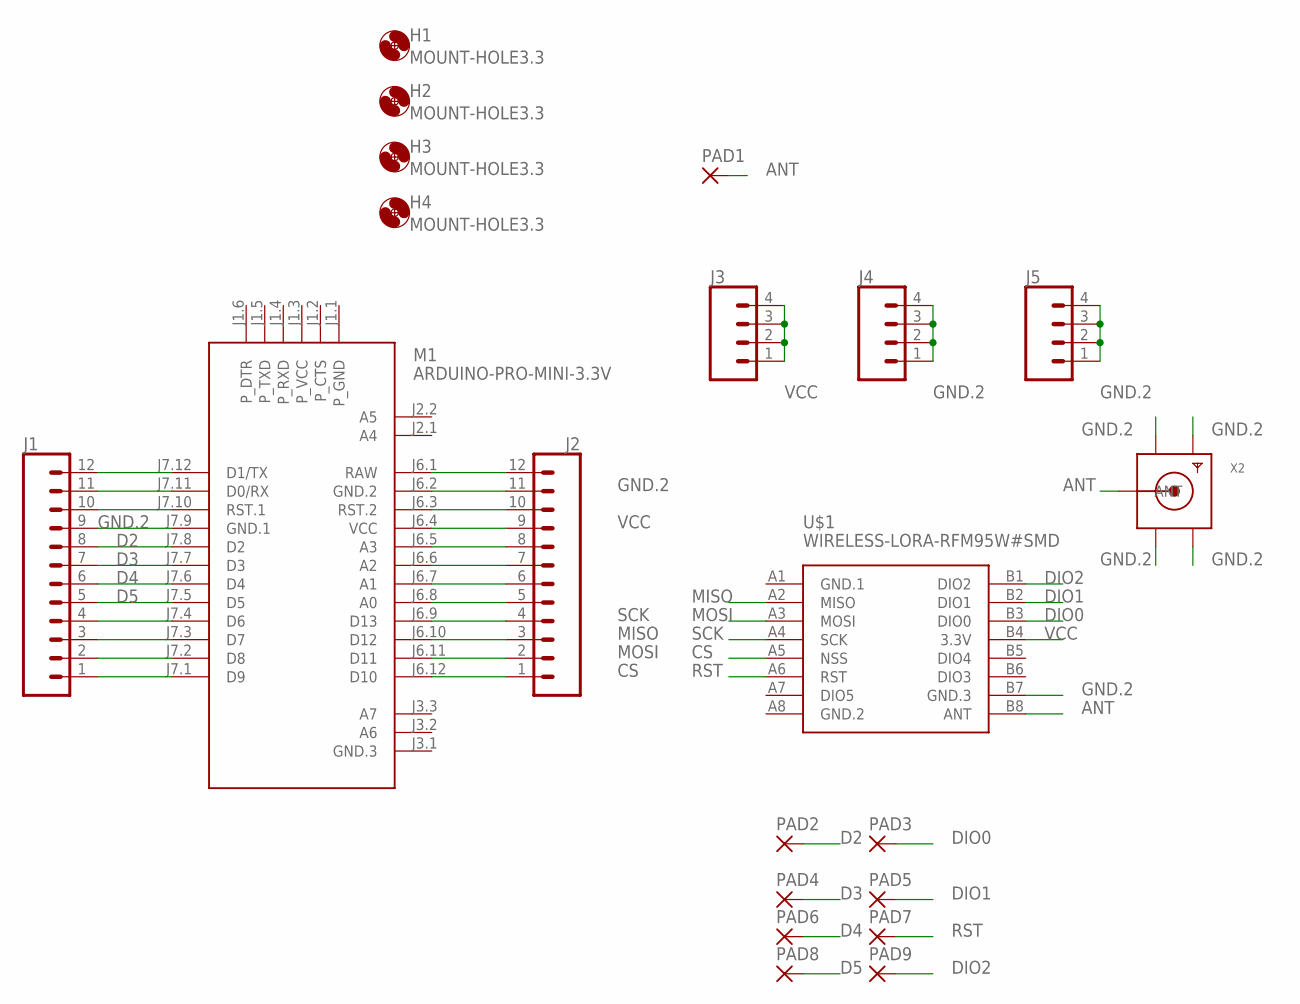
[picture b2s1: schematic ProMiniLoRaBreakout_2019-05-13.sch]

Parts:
H1, H2, H3, H4: MOUNT-HOLE3.3; 3,3
J1, J2: CONN_12; 1X12
J3, J4, J5: CONN_04; 1X04
M1: ARDUINO-PRO-MINI-3.3V; ARDUINO-PRO-MINI
PAD1: 2,15/1,0
PAD2, PAD3, PAD4, PAD5, PAD6, PAD7, PAD8, PAD9: SMD2; SMD1,27-2,54
U$1: WIRELESS-LORA-RFM95W#SMD
X2: SMACONNECTOR_EDGE_UFL; SMA_EDGELAUNCH_UFL

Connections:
ANT: PAD1.1, U$1.B8 (ANT), X2.P (ANT)
CS: J2.1, M1.J6.12 (D10), U$1.A5 (NSS)
D2: J1.8, M1.J7.8 (D2), PAD2.1
D3: J1.7, M1.J7.7 (D3), PAD4.1
D4: J1.6, M1.J7.6 (D4), PAD6.1
D5: J1.5, M1.J7.5 (D5), PAD8.1
DIO0: PAD3.1, U$1.B3 (DIO0)
DIO1: PAD5.1, U$1.B2 (DIO1)
DIO2: PAD9.1, U$1.B1 (DIO2)
GND.1: U$1.A1 (GND.1)
GND.2: J1.9, J2.11, J4.1, J4.2, J4.3, J4.4, J5.1, J5.2, J5.3, J5.4, M1.J6.2 (GND.2), M1.J7.9 (GND.1), U$1.A8 (GND.2), U$1.B7 (GND.3), X2.GND@1 (GND1), X2.GND@2 (GND2), X2.GND@3 (GND3), X2.GND@4 (GND4)
MISO: J2.3, M1.J6.10 (D12), U$1.A2 (MISO)
MOSI: J2.2, M1.J6.11 (D11), U$1.A3 (MOSI)
unnamed: J1.1, M1.J7.1 (D9)
unnamed: J1.2, M1.J7.2 (D8)
unnamed: J1.3, M1.J7.3 (D7)
unnamed: J1.4, M1.J7.4 (D6)
unnamed: J1.10, M1.J7.10 (RST.1)
unnamed: J1.11, M1.J7.11 (D0/RX)
unnamed: J1.12, M1.J7.12 (D1/TX)
unnamed: J2.6, M1.J6.7 (A1)
unnamed: J2.7, M1.J6.6 (A2)
unnamed: J2.8, M1.J6.5 (A3)
unnamed: J2.5, M1.J6.8 (A0)
unnamed: J2.10, M1.J6.3 (RST.2)
unnamed: J2.12, M1.J6.1 (RAW)
RST: PAD7.1, U$1.A6 (RST)
SCK: J2.4, M1.J6.9 (D13), U$1.A4 (SCK)
VCC: J2.9, J3.1, J3.2, J3.3, J3.4, M1.J6.4 (VCC), U$1.B4 (3.3V)

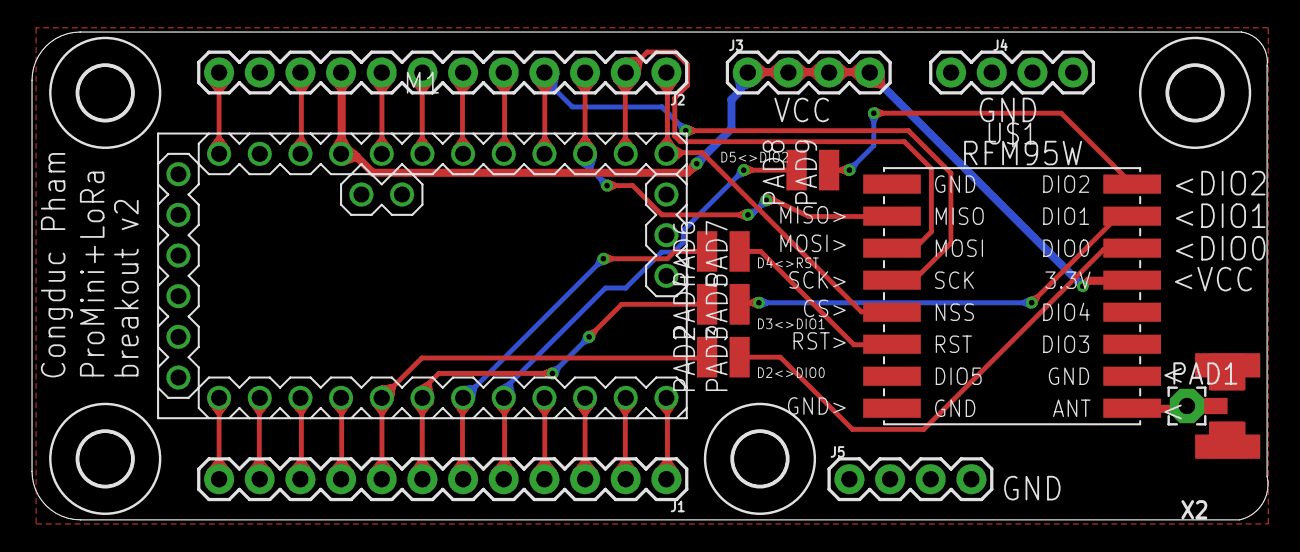
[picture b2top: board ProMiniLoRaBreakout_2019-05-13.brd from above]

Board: 2 copper layers, 77.2 x 30.5 mm, 21 parts (0 on the bottom side), 28 nets.

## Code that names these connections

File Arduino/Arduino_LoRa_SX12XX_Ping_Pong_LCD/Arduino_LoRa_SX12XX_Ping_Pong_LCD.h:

////////////////////////////////////////////////////////////////
#ifdef SX126X
//*******  Setup hardware pin definitions here ! ***************

//pinout is defined for our RFM95 PCB breakout used to host a NiceRF SX1262 module which almost the same pinout
//
#define NSS 10                                  //select pin on LoRa device
#define NRESET 4                                //reset pin on LoRa device
//we do not connect RFBUSY
//if you have a NiceRF SX1262 which has almost the same pinout than the RFM95 then
//you can use our ProMini LoRa PCB for RFM95 where RFBUSY (marked DIO2 on the RFM95 PCB) can be connected to D5
#define RFBUSY 5                                //busy pin on LoRa device 
//we do not connect DIO1 as we use polling method
//if you have a NiceRF SX1262 which has almost the same pinout than the RFM95 then
//you can use our ProMini LoRa PCB for RFM95 where DIO1 can be connected to D3
//in that case, comment #define USE_POLLING in SX126XLT.cpp to use DIO1 interrrupt pin
//#define DIO1 3                                  //DIO1 pin on LoRa device, used for RX and TX done
#define DIO1 -1                                  //DIO1 pin on LoRa device, used for RX and TX done
//*******
#define DIO2 -1                                 //DIO2 pin on LoRa device, normally not used so set to -1 
#define DIO3 -1                                 //DIO3 pin on LoRa device, normally not used so set to -1
#define RX_EN -1                                //pin for RX enable, used on some SX126X devices, set to -1 if not used
#define TX_EN -1                                //pin for TX enable, used on some SX126X devices, set to -1 if not used 
#define SW -1                                   //SW pin on some Dorji LoRa devices, used to power antenna switch, set to -1 if not used

#define LORA_DEVICE DEVICE_SX1262               //we need to define the device we are using

//*******  Setup LoRa Parameters Here ! ***************
//LoRa Modem Parameters
const uint32_t Frequency = 865200000;           //frequency of transmissions in hertz
const uint32_t Offset = 0;                      //offset frequency for calibration purposes
uint8_t Bandwidth = LORA_BW_125;          			//LoRa bandwidth
uint8_t SpreadingFactor = LORA_SF12;       			//LoRa spreading factor
uint8_t CodeRate = LORA_CR_4_5;           			//LoRa coding rate
const uint8_t Optimisation = LDRO_AUTO;         //low data rate optimisation setting, normally set to auto                               
#endif

////////////////////////////////////////////////////////////////
#ifdef SX127X
//*******  Setup hardware pin definitions here ! ***************

//pinout is defined for our RFM95 PCB breakout
//
#if defined ARDUINO_Heltec_WIFI_LoRa_32 || defined ARDUINO_WIFI_LoRa_32 || defined HELTEC_LORA
  // for the Heltec ESP32 WiFi LoRa module
#define NSS 18
#else
#define NSS 10                                  //select pin on LoRa device
#endif
#define NRESET 4                                //reset pin on LoRa device
//we do not connect DIO0 as we use polling method
//if you have an RFM95 then
//you can use our ProMini LoRa PCB for RFM95 where DIO0 can be connected to D2
//in that case, comment #define USE_POLLING in SX127XLT.cpp to use DIO0 interrrupt pin
//#define DIO0 2                                  //DIO0 pin on LoRa device, used for RX and TX done 
#define DIO0 -1                                  //DIO0 pin on LoRa device, used for RX and TX done 
//*******
#define DIO1 -1                                 //DIO1 pin on LoRa device, normally not used so set to -1 
#define DIO2 -1                                 //DIO2 pin on LoRa device, normally not used so set to -1

#define LORA_DEVICE DEVICE_SX1276               //we need to define the device we are using

//*******  Setup LoRa Parameters Here ! ***************
//LoRa Modem Parameters
const uint32_t Frequency = 865200000;           //frequency of transmissions in hertz
const uint32_t Offset = 0;                      //offset frequency for calibration purposes
const uint8_t Bandwidth = LORA_BW_125;          //LoRa bandwidth
const uint8_t SpreadingFactor = LORA_SF12;      //LoRa spreading factor
const uint8_t CodeRate = LORA_CR_4_5;           //LoRa coding rate
const uint8_t Optimisation = LDRO_AUTO;         //low data rate optimisation setting, normally set to auto

#define PABOOST                          
#endif

////////////////////////////////////////////////////////////////
#ifdef SX128X
//*******  Setup hardware pin definitions here ! ***************

//pinout is defined for our NiceRF SX1280 PCB breakout
//
#define NSS 10
#define NRESET 4
//we do not connect RFBUSY
//if you have a NiceRF SX1280
//you can use our ProMini LoRa PCB for SX1280 where RFBUSY is by default connected to D3
#define RFBUSY 3                                //busy pin on LoRa device 
//we do not connect DIO1 as we use polling method
//if you have a NiceRF SX1280
//you can use our ProMini LoRa PCB for SX1280 where DIO1 can be connected to D2
//in that case, comment #define USE_POLLING in SX128XLT.cpp to use DIO1 interrrupt pin
//#define DIO1 2                                  //DIO1 pin on LoRa device, used for RX and TX done
#define DIO1 -1                                  //DIO1 pin on LoRa device, used for RX and TX done
//*******
#define DIO2 -1                 								//not used 
#define DIO3 -1                 								//not used                      
#define RX_EN -1                								//pin for RX enable, used on some SX1280 devices, set to -1 if not used
#define TX_EN -1                								//pin for TX enable, used on some SX1280 devices, set to -1 if not used      

#define LORA_DEVICE DEVICE_SX1280               //we need to define the device we are using 

//*******  Setup LoRa Parameters Here ! ***************
//LoRa Modem Parameters
const uint32_t Frequency = 2403000000;           //frequency of transmissions in hertz
const uint32_t Offset = 0;                       //offset frequency for calibration purposes  
uint8_t Bandwidth = LORA_BW_0200;                //LoRa bandwidth
uint8_t SpreadingFactor = LORA_SF12;             //LoRa spreading factor
uint8_t CodeRate = LORA_CR_4_5;                  //LoRa coding rate                         

#define MAX_DBM                  10                 
#endif

#ifndef MAX_DBM
#define MAX_DBM                 14
#endif

#define DEFAULT_DEST_ADDR       1

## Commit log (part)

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2017-10-05 update README with links to 2 new tutorial videos
2017-10-13 update Arduino example
2017-11-03 update README files, fix MD5 digest computation of gw id, always use pin 10 on Arduino boards for CS pin
2017-11-07 back to CRC off
2017-11-08 fix CRC on receiver, especially for the gateway
2017-11-08 update README, add examples
2017-11-10 update README and example sketch for RadioHead lib
2017-11-20 Add Node-Red support
2017-11-21 add Images folder
2017-11-21 update README with images
2017-11-21 add MQTT cloud
2017-11-21 update cloud scripts
2017-11-22 update distrib to support LoRaWAN 4-byte devAddr
2017-11-23 update cloud and update scripts
2017-11-27 update for ESP8266
2017-11-28 update README for Node-Red
2017-11-30 update Node-Red support
2017-12-03 update MQTT and Node-Red clouds
2017-12-03 update LoRaWAN encrypted for MQTT and Node-Red clouds
2017-12-07 add timestamp in entity creation with CloudOrion.py
2017-12-07 update test folder
2017-12-08 update update_gw.sh script
2017-12-21 Add CloudGpsFile.py and restructuration of post_processing_gw.py to ease definition of periodic tasks
2017-12-27 update with WiFi client README and command
2017-12-28 update web interface and README for WiFi client feature
2017-12-29 update READMEs, re-structuration of information
2017-12-29 update READMEs
2017-12-31 update web admin interface
2018-01-01 update README, CloudGpsFile.py and test folder
2018-01-02 bug fix in SX1272.cpp
2018-01-09 update CloudGpsFile.py and add dynamic GPS support
2018-01-10 Minor to fix display of output
2018-01-12 update image
2018-01-15 Update cloud scripts and add folder for gps and Node-Red
2018-01-15 update startup script
2018-01-19 update PingPong example and README, update SX1272 lib for devices
2018-02-22 update examples
2018-03-02 update distrib with some enhanced downlink features, add CloudNewOrion.py for WAZIUP testing
2018-03-03 Update Arduino_LoRa_Simple_temp and README
2018-03-04 Update CloudThingSpeak.py, fix bug in post_processing_gw.py and update README
2018-03-06 update CloudThingSpeak.py and REAME
2018-03-11 Correct small bug in post_processing_gw.py
2018-03-14 Update gw web admin interface
2018-03-21 Update Arduino README
2018-03-23 update Arduino examples
2018-03-29 Update Orion and WAZIUP clouds, fix SX1272 lib
2018-03-29 Update gateway web admin interface
2018-03-31 Update carrier sense procedure in SX1272 lib
2018-03-31 Update with ngrok tool for remote access
2018-04-06 Update for better WAZIUP support
2018-04-08 Update for better WAZIUP support and explanation
2018-05-18 Add ESP8266 - NodeMCU support
2018-05-29 update configuration files and MongoDB web interface
2018-05-29 Update web data interface
2018-06-12 update CloudWAZIUP.py script
2018-06-12 update scripts for handling gateway github version
2018-06-12 update scripts and config file for handling gateway github version
2018-06-12 update scripts
2018-06-15 update scripts and web admin interface
2018-06-21 update distribution
2018-06-22 update tutorials
2018-07-10 update generic sensor example
2018-07-12 update Arduino examples and 3GDongle scripts
2018-07-25 update README with link to a new live demo video
2018-08-05 Update GPS/CloudGpsFile related features
2018-08-28 Add U8x8lib
2018-08-28 Add a small delay in the availableData() loop, see https://github.com/CongducPham/LowCostLoRaGw/issues/211
2018-09-06 update Arduino example and README
2018-09-06 update Arduino examples and README
2018-09-08 Update start_gw.sh script
2018-09-12 Adding user-defined repository for update
2018-09-20 upate Arduino_LoRa_Generic_Sensor
2018-10-05 update SX1272 library
2018-10-28 update CloudWAZIUP.py and key_WAZIUP.py for new API
2018-10-28 update CloudWAZIUP.py, key_WAZIUP.py and web admin interface for new WAZIUP API
2018-11-04 update with PCBs information
2018-11-14 update distrib
2018-11-21 add shutdown button feature
2018-11-25 fix bug in gw admin interface to handle space ch. in SSID
2019-01-03 update support of Loranga 3G board
2019-01-07 add fast stats with OLED, update support of Loranga 2G/3G
2019-01-16 add Lightweight Steeam Cipher encryption support
2019-01-17 update Lightweight Steeam Cipher encryption support
2019-01-18 update LSC lib and related examples
2019-02-01 update Arduino InteractiveDevice
2019-02-25 update SX1272.cpp for gateway
2019-03-14 update to compile correctly for RPI3B+
2019-03-23 fix bugs and update the LoRaWAN support
2019-03-29 update for LoRaWAN and TTN support
2019-03-31 update the LoRaWAN support
2019-03-31 update web interface for LoRaWAN support
2019-03-31 fix bug in gateway id setting
2019-04-07 fix various minor bugs in web admin interface
2019-04-22 fix minor reset bug in SX1272.cpp, RST pin on RPI is GPIO4
2019-04-23 update Arduino_LoRa_temp
2019-04-25 update post_processing and arduino example
2019-05-09 update Arduino lib
2019-05-10 update Arduino_LoRa_temp and README
2019-05-10 update Arduino_LoRa_LMIC_ABP_temp
2019-05-14 update PCB images
2019-05-14 update PCBs
2019-05-16 update web interface and update procedure
2019-05-16 fix typo for fast stats
2019-05-21 update CloudWAZIUP.py and Arduino examples
2019-05-21 update LMIC lib
2019-05-22 update scripts and READMEs
2019-05-23 update support of multi-channel gateway such as RAK831/2245
2019-06-06 update RAK831/2245 support
2019-06-18 update WAZIUP cloud
2019-07-19 update Arduino GPS example
2019-07-22 update CloudWAZIUP
2019-10-29 Update CloudTTN.py to use 2019-10-28T10:28:02.0585678Z date format
2019-11-09 use python -B to allow changes in key_* cloud file
2019-11-10 add sys.dont_write_bytecode = True to allow dynamic modification of key_* file
2019-11-11 update local decryption process for both LoRaWAN packet and encapsulated encrypted packet
2019-11-12 update link to SD card image
2019-11-12 update key handling for LoRaWAN devices
2019-11-12 update decryption scripts
2019-11-13 add custom MQTT port feature
2019-11-14 update web interface and RAK install script
2019-11-25 update to support Debian Buster
2019-11-29 update internet pending message procedure
2019-12-11 update links
2019-12-18 update scripts and networking scripts
2019-12-27 update with ChirpStack support
2020-01-04 update web admin interface with easy LoRaWAN configuration
2020-01-06 update README for new SD card image based on Buster
2020-01-28 support of LoRaWAN downlink and OTAA for single-channel gateway
2020-01-31 update SX1272 lib for Arduino
2020-02-03 fix file permission
2020-02-04 update to have basic support of LoRaWAN EU433MHz band
2020-02-11 update Arduino example and images
2020-02-20 update Arduino_LoRa_temp with LoRaWAN downlink support
2020-02-29 update downlink support
2020-03-02 improve WiFi client/AP management
2020-05-19 update lora_gateway with better frequency management
2020-06-22 update README with EU News
2020-09-03 update PCB file
2020-10-31 fix getToA() in SX1272.cpp
2020-10-31 update SX1272.h with IQ inversion
2020-10-31 Add SX12XX and dedicated examples for Arduino to support SX12XX LoRa chip
2020-10-31 Update SX12XX examples
2020-10-31 Move to SX12XX library to support SX126X, SX127X and SX128X LoRa chip
2020-11-03 Update SX12XX support
2020-11-04 Update new SX12XX support for LoRaWAN ABP/OTAA
2020-11-04 minor fix in SX12XX related files
2020-11-05 update SX12XX related files
2020-11-05 update SX126X and SX128X time-on-air computation
2020-11-07 update SX12XX lib and add SX12XX examples
2020-11-10 update SX12XX gateway
2020-11-12 update SX12XX-related information and add SX12XX examples
2020-11-14 update SX12XX and PCBs
2020-11-16 update for SX128X
2020-11-16 harmonisation of code
2020-11-17 update web interface, compilation & update scripts
2020-11-17 update Carrier Sense mechanism for SX126X, SX127X and SX128X
2020-11-19 update for PHP7
2020-11-21 update PCB
2020-11-25 update SX12XX related files and examples
2020-11-26 update ranging examples
2020-12-03 minor fix in SX12XX related files, add Arduino examples
2020-12-17 docs: fix simple typo, compenstation -> compensation
    There is a small typo in Arduino/libraries/U8g2/src/clib/u8x8_d_uc1604.c, Arduino/libraries/U8g2/src/clib/u8x8_d_uc1608.c.
    Should read `compensation` rather than `compenstation`.
2020-12-19 Update examples, add collision avoidance mechanism
2020-12-21 add low power mode for collision avoidance
2020-12-24 update Arduino example with separate low power function
2020-12-29 update SX12XX Collision Avoidance mechanism
2021-01-18 add wiringPi for 64-bit OS to prepare support for 64-bit OS
2021-01-21 add SPI lib based on wiringPi to support 64-bit OS
2021-01-21 update README for compilation procedure
2021-01-24 update README with compilation options
2021-01-25 update modified version for RPI4 of wiringPi 64-bit
2021-10-01 update README for embedded AI framework
2021-10-01 Update README with correct link to 64-bit OS SD card image
2021-10-27 Update README for https
2021-11-23 Minor fixes in Arduino examples
2021-12-10 fix SF and BW display on OLED
2021-12-25 Update links to SD card images
2022-01-22 Add captive wifi portal with nodogsplash
2022-01-22 Update captive WiFi portal README
2022-01-22 Add screenshoot
2022-05-13 Fix typo generating bugs
2022-11-22 Update README and links to SD card images
2022-12-01 Update for wiringPi for RPI4 and/or 64-bit OS
2022-12-01 Update link to download wiringPi
2022-12-03 Update links for SD card images
2025-03-23 Last commit – check our last development
2025-05-04 Arduino code for testing ABP on TTN
2025-05-04 Create payload.txt
    Javascript Payload Decoder TTN
2025-05-04 Initial
2026-04-21 Removed PIGPIO_OLD folder

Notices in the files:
parts and their libraries:
diy-modules: Released under the Creative Commons Attribution 4.0 International License: http://creativecommons.org/licenses/by/4.0
SparkFun-Connectors: Licensing: Creative Commons ShareAlike 4.0 International - https://creativecommons.org/licenses/by-sa/4.0
